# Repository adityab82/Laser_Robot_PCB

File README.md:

# Dual H-Bridge Motor Driver PCB for Laser Animations

## Overview
This project involves the design and implementation of a **dual H-bridge circuit** to control two motors. The motors manipulate the position of a laser beam, allowing the creation of animations on a screen. The PCB was designed, soldered, and thoroughly tested to ensure precise and reliable operation.

## Features
- **Dual H-Bridge Circuit**: Controls two motors independently for precise laser beam positioning.
- **PCB Design**: Created using KiCad, ensuring a compact and functional layout.
- **Testing and Debugging**: The PCB was soldered and extensively debugged using an oscilloscope and multimeter to ensure full functionality.

## Images
All images related to the project, including PCB schematics, layout, 3D rendering and final soldered board, can be found in the `Img` folder.

## Tools Used
- **KiCad**: For schematic capture and PCB layout. 
- **Oscilloscope & Multimeter**: For testing and debugging.

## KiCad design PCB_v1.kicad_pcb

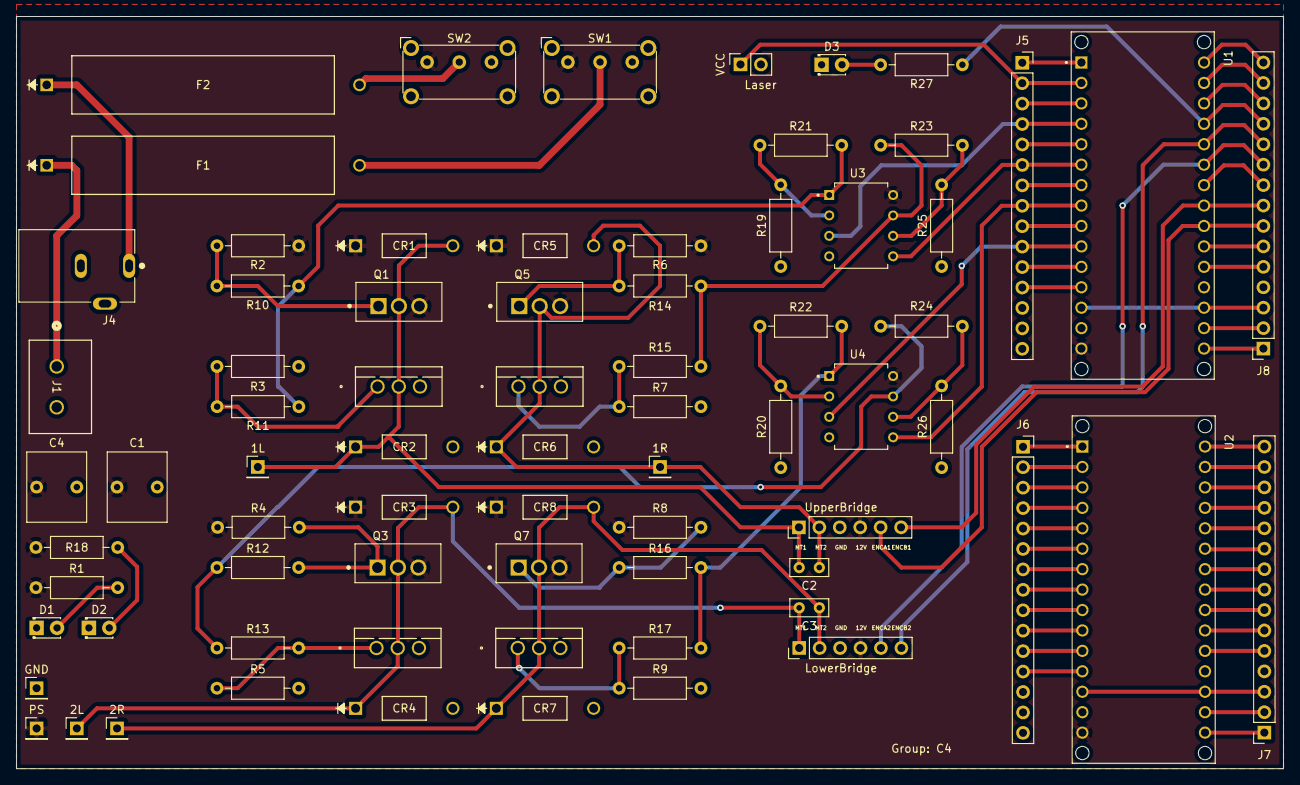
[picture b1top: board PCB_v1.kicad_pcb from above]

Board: 2 copper layers, 157.5 x 93.5 mm, 73 parts (0 on the bottom side), 81 nets.

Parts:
1L: TP_1L; PinHeader_1x01_P2.54mm_Vertical
1R: TP_1R; PinHeader_1x01_P2.54mm_Vertical
2L: TP_2L; PinHeader_1x01_P2.54mm_Vertical
2R: TP_2R; PinHeader_1x01_P2.54mm_Vertical
C1, C4: 10uF; C_Rect_L7.2mm_W8.5mm_P5.00mm_FKP2_FKP2_MKS2_MKP2
C2, C3: 100nF; C_Rect_L4.6mm_W2.0mm_P2.50mm_MKS02_FKP02
CR1, CR2, CR3, CR4, CR5, CR6, CR7, CR8: MBR150RLG; MBR150x
D1, D2, D3: LED; LED_D1.8mm_W3.3mm_H2.4mm
F1, F2: Fuse; fuse_tht
GND: GND_TP; PinHeader_1x01_P2.54mm_Vertical
J1: OSTTC022162; CONN_OSTTC022162_OST
J4: PJ-102A; CUI_PJ-102A
J5, J6, J7, J8: Conn_01x15_Female; PinSocket_1x15_P2.54mm_Vertical
Laser: Conn_01x02_Female; PinSocket_1x02_P2.54mm_Vertical
LowerBridge: Conn_01x06_Male; PinHeader_1x06_P2.54mm_Vertical
PS: PowerSupply_TP; PinHeader_1x01_P2.54mm_Vertical
Q1, Q3, Q5, Q7: Q_PMOS_GDS; FQP47P06
Q2, Q4, Q6, Q8: Q_NMOS_GDS; N-mos
R1, R18, R27: 500; R_Axial_DIN0207_L6.3mm_D2.5mm_P10.16mm_Horizontal
R2, R3, R4, R5, R6, R7, R8, R9: 10k; R_Axial_DIN0207_L6.3mm_D2.5mm_P10.16mm_Horizontal
R10, R11, R12, R13, R14, R15, R16, R17: 100; R_Axial_DIN0207_L6.3mm_D2.5mm_P10.16mm_Horizontal
R19, R20, R25, R26: 2k; R_Axial_DIN0207_L6.3mm_D2.5mm_P10.16mm_Horizontal
R21, R22, R23, R24: 5.1k; R_Axial_DIN0207_L6.3mm_D2.5mm_P10.16mm_Horizontal
SW1, SW2: SW_SPDT; SW_E-Switch_EG1224_SPDT_Angled
U1, U2: ABX00027; MODULE_ABX00028
U3, U4: TL072CDT; opamp
UpperBridge: Conn_01x06_Male; PinHeader_1x06_P2.54mm_Vertical

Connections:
+12V: C1.1, C4.1, CR1.1 (CATHODE), CR3.1 (CATHODE), CR5.1 (CATHODE), CR8.1 (CATHODE), LowerBridge.4, PS.1, Q1.3 (S), Q3.3 (S), Q5.3 (S), Q7.3 (S), R1.1, R2.1, R4.1, R6.1, R8.1, R18.1, SW1.1 (A), SW2.1 (A), U1.15 (VIN), U2.15 (VIN), U3.8 (VCC+), U4.8 (VCC+), UpperBridge.4
/1: J6.1, U2.1 (D13)
/1_1: J5.1, U1.1 (D13)
/2: J6.2, U2.2 (+3V3)
/12: J6.12, U2.12 (VUSB)
/12_1: J5.12, U1.12 (VUSB)
/16: J7.1, U2.16 (TX)
/16_1: J8.1, U1.16 (TX)
/17: J7.2, U2.17 (RX)
/17_1: J8.2, U1.17 (RX)
/18: J7.3, U2.13 (~RESET), U2.18 (~RESET)
/18_1: J8.3, U1.13 (~RESET), U1.18 (~RESET)
/ENC_A: J8.7, U1.22 (D4), UpperBridge.5
/ENC_A2: J8.10, LowerBridge.5, U1.25 (D7)
/ENC_B: J8.8, U1.23 (D5/PWM), UpperBridge.6
/ENC_B2: J8.11, LowerBridge.6, U1.26 (D8)
/Laser_VCC: J5.2, Laser.1, U1.2 (+3V3)
/PWM1: R10.1, R11.1, R21.2, U3.1 (OUTPUT1)
/PWM1_3.3: J5.4, U1.4 (A0/DAC0), U3.3 (NON-INVERTING_INPUT1)
/PWM2: R14.2, R15.2, R23.1, U3.7 (OUTPUT2)
/PWM2_3.3: J5.6, U1.6 (A2), U3.5 (NON-INVERTING_INPUT2)
/PWM3: R12.1, R13.1, R24.1, U4.7 (OUTPUT2)
/PWM3_3.3: J5.8, U1.8 (A4/SDA), U4.5 (NON-INVERTING_INPUT2)
/PWM4: R16.2, R17.2, R22.2, U4.1 (OUTPUT1)
/PWM4_3.3: J5.10, U1.10 (A6), U4.3 (NON-INVERTING_INPUT1)
/state: J8.12, R27.1, U1.27 (D9/PWM)
GND: C1.2, C4.2, CR2.2 (ANODE), CR4.2 (ANODE), CR6.2 (ANODE), CR7.2 (ANODE), D1.1 (K), D2.1 (K), D3.1 (K), GND.1, J1.2, J4.2, Laser.2, LowerBridge.3, Q2.3 (S), Q4.3 (S), Q6.3 (S), Q8.3 (S), R3.2, R5.2, R7.2, R9.2, R19.1, R20.1, R25.1, R26.1, U1.14 (GND), U1.19 (GND), U2.14 (GND), U2.19 (GND), U3.4 (VCC-), U4.4 (VCC-), UpperBridge.3
unnamed: 1R.1, C2.1, CR5.2 (ANODE), CR6.1 (CATHODE), Q5.2 (D), Q6.2 (D), UpperBridge.2
unnamed: 1L.1, C2.2, CR1.2 (ANODE), CR2.1 (CATHODE), Q1.2 (D), Q2.2 (D), UpperBridge.1
unnamed: 2R.1, C3.1, CR7.1 (CATHODE), CR8.2 (ANODE), LowerBridge.2, Q7.2 (D), Q8.2 (D)
unnamed: 2L.1, C3.2, CR3.2 (ANODE), CR4.1 (CATHODE), LowerBridge.1, Q3.2 (D), Q4.2 (D)
unnamed: D1.2 (A), R1.2
unnamed: D2.2 (A), R18.2
unnamed: D3.2 (A), R27.2
unnamed: F1.1, J1.1
unnamed: F1.2, SW1.2 (B)
unnamed: F2.1, J4.1
unnamed: F2.2, SW2.2 (B)
unnamed: J5.3, U1.3 (AREF)
unnamed: J5.5, U1.5 (A1)
unnamed: J5.7, U1.7 (A3)
unnamed: J5.9, U1.9 (A5/SCL)
unnamed: J5.11, U1.11 (A7)
unnamed: Q1.1 (G), R2.2, R10.2
unnamed: Q2.1 (G), R3.1, R11.2
unnamed: Q3.1 (G), R4.2, R12.2
unnamed: Q4.1 (G), R5.1, R13.2
unnamed: Q5.1 (G), R6.2, R14.1
unnamed: Q6.1 (G), R7.1, R15.1
unnamed: Q7.1 (G), R8.2, R16.1
unnamed: Q8.1 (G), R9.1, R17.1
unnamed: R19.2, R21.1, U3.2 (INVERTINGINPUT1)
unnamed: R20.2, R22.1, U4.2 (INVERTINGINPUT1)
unnamed: R23.2, R25.2, U3.6 (INVERTINGINPUT2)
unnamed: R24.2, R26.2, U4.6 (INVERTINGINPUT2)
unnamed: J8.5, U1.20 (D2)
unnamed: J8.6, U1.21 (D3/PWM)
unnamed: J8.9, U1.24 (D6/PWM)
unnamed: J8.13, U1.28 (D10/PWM)
unnamed: J8.14, U1.29 (D11/MOSI)
unnamed: J8.15, U1.30 (D12/MISO)
unnamed: J6.3, U2.3 (AREF)
unnamed: J6.4, U2.4 (A0/DAC0)
unnamed: J6.5, U2.5 (A1)
unnamed: J6.6, U2.6 (A2)
unnamed: J6.7, U2.7 (A3)
unnamed: J6.8, U2.8 (A4/SDA)
unnamed: J6.9, U2.9 (A5/SCL)
unnamed: J6.10, U2.10 (A6)
unnamed: J6.11, U2.11 (A7)
unnamed: J7.5, U2.20 (D2)
unnamed: J7.6, U2.21 (D3/PWM)
unnamed: J7.7, U2.22 (D4)
unnamed: J7.8, U2.23 (D5/PWM)
unnamed: J7.9, U2.24 (D6/PWM)
unnamed: J7.10, U2.25 (D7)
unnamed: J7.11, U2.26 (D8)
unnamed: J7.12, U2.27 (D9/PWM)
unnamed: J7.13, U2.28 (D10/PWM)
unnamed: J7.14, U2.29 (D11/MOSI)
unnamed: J7.15, U2.30 (D12/MISO)

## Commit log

2025-01-11 completed PCB for laser animation robot
2025-01-11 added soldered board images
2025-01-11 added README
